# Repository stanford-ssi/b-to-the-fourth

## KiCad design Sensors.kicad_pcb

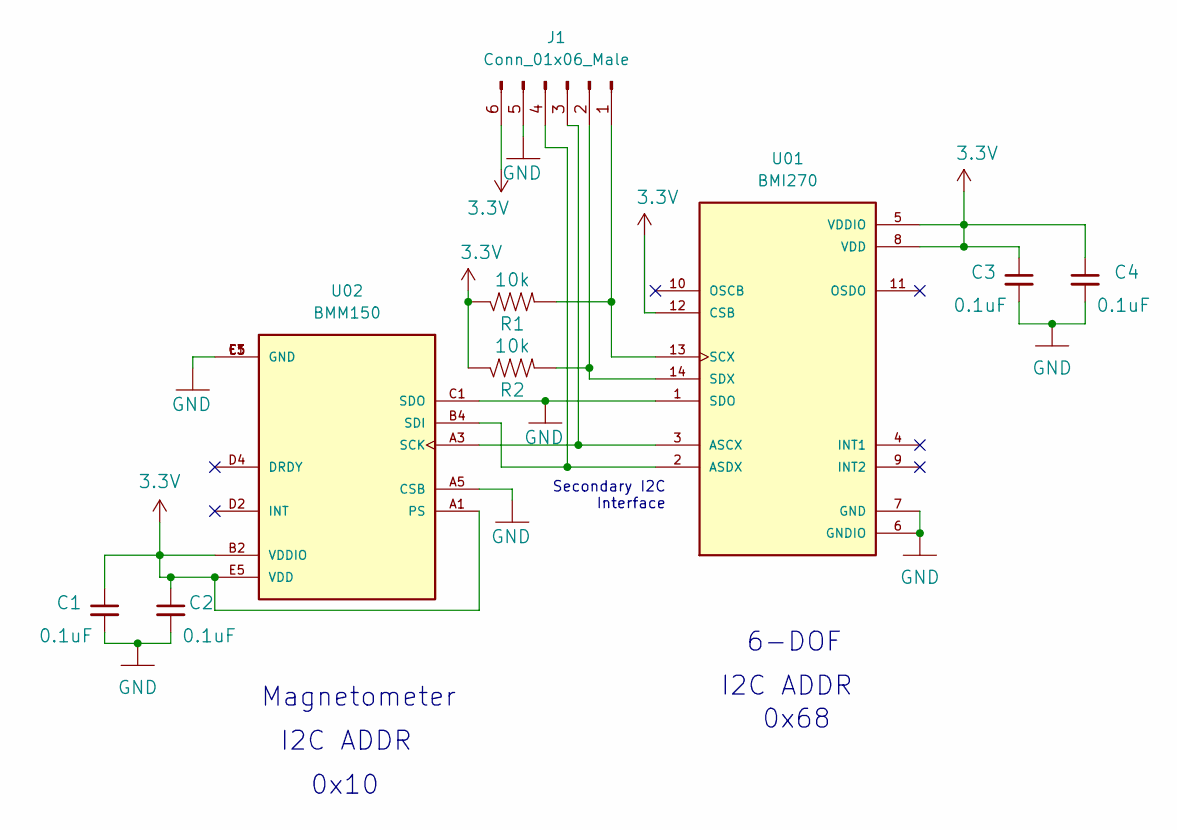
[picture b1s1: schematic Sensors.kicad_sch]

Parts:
C1, C2, C3, C4: 0.1uF; C_0603_1608Metric
J1: Conn_01x06_Male
R1, R2: 10k; R_0603_1608Metric
U01: BMI270; XDCR_BMI270
U02: BMM150; XDCR_BMM150

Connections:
3.3V: C1.1, C2.1, C3.1, C4.1, J1.6, R1.1, R2.1, U01.5 (VDDIO), U01.8 (VDD), U01.12 (CSB), U02.A1 (PS), U02.B2 (VDDIO), U02.E5 (VDD)
GND: C1.2, C2.2, C3.2, C4.2, J1.5, U01.1 (SDO), U01.6 (GNDIO), U01.7 (GND), U02.A5 (CSB), U02.C1 (SDO), U02.C5 (GND), U02.E1 (GND), U02.E3 (GND)
unnamed: J1.4, U01.2 (ASDX), U02.B4 (SDI)
unnamed: J1.3, U01.3 (ASCX), U02.A3 (SCK)
unnamed: J1.1, R1.2, U01.13 (SCX)
unnamed: J1.2, R2.2, U01.14 (SDX)

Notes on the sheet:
0x10
Secondary I2C Interface
I2C ADDR
0x68
Magnetometer
6-DOF

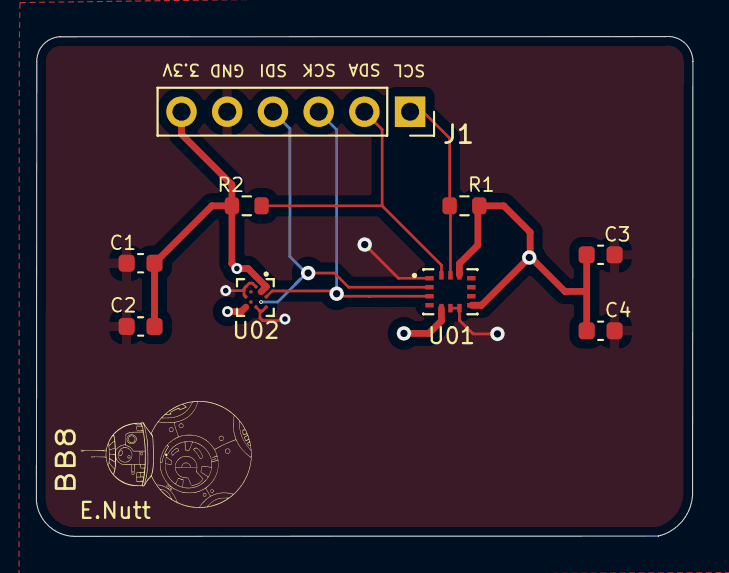
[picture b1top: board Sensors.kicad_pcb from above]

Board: 4 copper layers, 36.5 x 27.8 mm, 9 parts (0 on the bottom side), 6 nets.

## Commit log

2023-01-14 initial schematic
2023-01-14 add datasheets
2023-01-14 01_14 edits
2023-01-18 with layout, ready for review
2023-01-18 with fills bc i no remember
2023-01-24 biggie cheese
2023-01-24 biggEE cheese
2023-01-24 final gbr
